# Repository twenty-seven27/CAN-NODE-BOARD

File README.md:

# CAN Node Board — rev A

One custom PCB that replaces the Arduino Mega + CAN Bus Shield stack on every node of a 4WD autonomous parking robot. The robot's three nodes (sensor, receive, motor) talk over CAN; each one now runs the **same board and the same firmware image**, and a single resistor tells the board which node it is.

| | |
|---|---|
| Input | 6–16 V (2S/3S LiPo, 6–8 AA, 12 V bench), reverse-polarity protected, TVS clamped |
| Rails | 5 V / 2 A synchronous buck (servo, ultrasonic sensor, CAN transceiver) · 3.3 V LDO (logic) |
| MCU | STM32G431KBT6 — Cortex-M4F 170 MHz, FDCAN, hardware quadrature-encoder timers |
| CAN | TCAN1042V transceiver, 5 V bus side / 3.3 V logic (VIO), 500 kbit/s classic CAN |
| Board | 76 × 56 mm, 4 layers (signal / GND / 3.3 V / signal), 4 × M3 holes |
| I/O | Servo, HC-SR04 ultrasonic, 2 × wheel encoder, motor driver (PWM + DIR × 2), UART, 2 spare GPIO, SWD |

## The feature worth pointing out: one PCB, one firmware image, every node

PB0 (an ADC input) sits in the middle of a divider: a fixed 10 kΩ pull-up (R4) and a **role resistor R5** to ground. At boot the firmware averages eight ADC samples, picks the nearest bin, and from that sets its CAN IDs, acceptance filters and which peripherals it starts.

| R5 fitted | V(ROLE) | Role |
|---|---|---|
| 0 Ω | 0.00 V | Sensor node (ultrasonic + servo) |
| 3.3 kΩ | 0.82 V | Receive node |
| 10 kΩ | 1.65 V | Motor node (encoders + motor driver) |
| 33 kΩ | 2.53 V | Spare |
| not fitted | 3.30 V | **Safe mode**: CAN listen-only, all outputs off |

- One pin carries five roles. Bins are about 0.8 V apart, so 5 % resistors can never land in the wrong one.
- Nothing to bump or misconfigure later, unlike a DIP switch, and it costs one 0603 part.
- An unfitted board fails safe: it can never drive the motors by accident.
- The same idea runs through the rest of the board: the transceiver's STB pin is pulled **high**, so a node stays off the bus until its firmware is ready, and CAN termination is a pair of solder jumpers (JP1 + JP2, split 2 × 60.4 Ω + 4.7 nF) closed only on the two end-of-bus boards. Every board is identical until it is configured.

The role table is printed on the back silkscreen, so the board documents itself.

## Block diagram

```mermaid
flowchart LR
  BUS["Bus connectors J1/J2<br/>VBAT · GND · CAN-H · CAN-L<br/>(daisy-chained)"] -->|VBAT| PG["Reverse-polarity P-FET Q1<br/>+ Zener D1, TVS D2"]
  PG -->|VIN_PROT| BUCK["5 V buck U1<br/>AP63205, 2 A"]
  BUCK -->|+5V| LDO["3.3 V LDO U2<br/>AP2112K-3.3"]
  BUCK -->|+5V| IO
  BUS <-->|CAN-H/L| XCVR["CAN transceiver U4<br/>TCAN1042V"]
  XCVR --- TERM["Split termination<br/>JP1/JP2, end nodes only"]
  XCVR <-->|TX/RX, STB| MCU["STM32G431KBT6 U3<br/>FDCAN · TIM encoders · ADC"]
  LDO -->|+3V3| MCU
  ROLE["Role select<br/>R4 + R5 → PB0"] --> MCU
  MCU --> IO["Headers: servo, ultrasonic,<br/>encoders, motor, UART, AUX"]
  SWD["SWD J10 (ST-Link)"] --- MCU
```

## Design decisions

**MCU and pins.** The STM32G431 has FDCAN built in (no separate CAN controller as on the MCP2515 shield) and timers with a hardware quadrature-encoder mode for the wheel encoders. On the 32-pin package, FDCAN TX only exists on PA12, which is also USB D+, so CAN and USB cannot both be used. The board drops USB and is programmed over SWD (ST-Link or a Nucleo's built-in one), with a 3-pin UART header for serial debug. PB8 doubles as BOOT0 and is pulled low, so the board always boots from flash.

| Pin | Function |
|---|---|
| PA11 / PA12 | FDCAN1 RX / TX |
| PA13 / PA14 | SWDIO / SWCLK |
| PA2 / PA3 | USART2 TX / RX (debug) |
| PB0 | ADC1_IN15, role select |
| PA0 | TIM2_CH1 input capture (ultrasonic echo, 32-bit timer) |
| PA1 | Ultrasonic trigger |
| PB4 | TIM16_CH1 servo PWM, 50 Hz |
| PA8 / PA9 | TIM1_CH1 / CH2 motor PWM, ~20 kHz |
| PA4 / PA5 | Motor direction |
| PB6 / PB7 | TIM4 encoder mode (left) |
| PA6 / PA7 | TIM3 encoder mode (right) |
| PF0 / PF1 | 8 MHz crystal (HSE) |
| PA10 | Status LED |
| PA15 | Transceiver STB |
| PB3 / PB5 | Spare GPIO on the AUX header |

The servo and the motors run on **different timers** because channels on one timer share a period: a servo needs 50 Hz, a motor driver about 20 kHz.

**Clock.** CAN bit timing needs a tighter clock than the internal RC oscillator gives, so an 8 MHz crystal drives the PLL. Load capacitors: C = 2 × (C_L − C_stray) = 2 × (10 − 3) pF ≈ 15 pF; match them to the crystal actually fitted.

**Power.** Q1 (AO3407A, −30 V, V_GS ±20 V) protects against a reversed battery with almost no voltage drop; the body diode conducts first, then the gate (pulled to ground through R1) turns the FET fully on. D1 clamps V_GS to 12 V and D2 (SMAJ18CA) clamps input transients from the motors. The buck uses the datasheet's typical-application values (10 µF in, 4.7 µH, 2 × 22 µF out, 100 nF bootstrap). C1 (47 µF) damps the input cable's inductance and C17 (220 µF) sits at the servo header to absorb stall-current spikes. VDDA is fed through a ferrite bead because the role pin is an analog measurement.

**Interfaces.** The HC-SR04 echo is a 5 V signal, divided to 3.33 V by R8/R9 (1 k / 2 k). Encoders are powered at 3.3 V with 10 kΩ pull-ups, which suits open-collector Hall encoders; if yours need 5 V, check that their outputs stay within the MCU's input limits. The motor header supplies 5 V for driver logic and takes 3.3 V PWM/DIR.

**Layout.** Four layers: In1 is an unbroken ground plane under everything, In2 is the 3.3 V plane, and the outer layers carry signals with ground pours. Every surface-mount ground and 3.3 V pad has its own via to its plane. The buck's input capacitor sits right next to its VIN and GND pins and the switch node is a short, wide copper run to the inductor. Power nets use 0.6–0.8 mm tracks, CAN-H/L 0.25 mm, signals 0.2 mm, with 0.2 mm clearance and 0.6/0.3 mm vias, all within standard 4-layer capabilities at JLCPCB and PCBWay.

## Verification status

- Schematic connectivity checked against the intended netlist (all 43 nets match); every power-input net has a driver or power flag.
- PCB DRC (KiCad 7.0.11): **0 violations, 0 unconnected pads, 0 footprint errors**.
- **Not yet fabricated or tested.** Bring-up plan for the first boards:
  1. Check for shorts between VBAT, 5 V, 3.3 V and GND before applying power.
  2. Power from a current-limited bench supply (12 V, 100 mA limit) and check 5 V and 3.3 V.
  3. Flash a blink + role-readout firmware over SWD; confirm the status LED blinks the role number.
  4. Two boards on a short bus with JP1/JP2 closed at each end: send and receive frames at 500 kbit/s.
  5. Connect the servo, sensor, encoders and motor driver one at a time.

## Files

| Path | Contents |
|---|---|
| `kicad/` | KiCad project: schematic, PCB, project symbol library (TCAN1042V) |
| `docs/schematic.pdf` | Schematic, one A3 sheet |
| `docs/render-3d.png`, `render-top.png`, `render-bottom.png` | Board renders |
| `docs/layout-top.png`, `layout-bottom.png` | Copper and silkscreen plots (pours hidden) |
| `docs/can-node.step` | 3D model of the assembled board |
| `fab/can-node-gerbers.zip` | Gerbers (4 layers) + Excellon drill files, origin at the board's bottom-left corner |
| `fab/can-node-bom.csv` | Bill of materials (part numbers are examples; R5 is fitted per role) |
| `fab/can-node-cpl.csv` | Pick-and-place positions for assembly |

Ordering: 4 layers, 1.6 mm FR-4, 1 oz outer copper, any surface finish. Upload `can-node-gerbers.zip` as-is.

Designed in KiCad 7; the project opens in KiCad 8 and 9 (KiCad offers to upgrade the file format on first save).

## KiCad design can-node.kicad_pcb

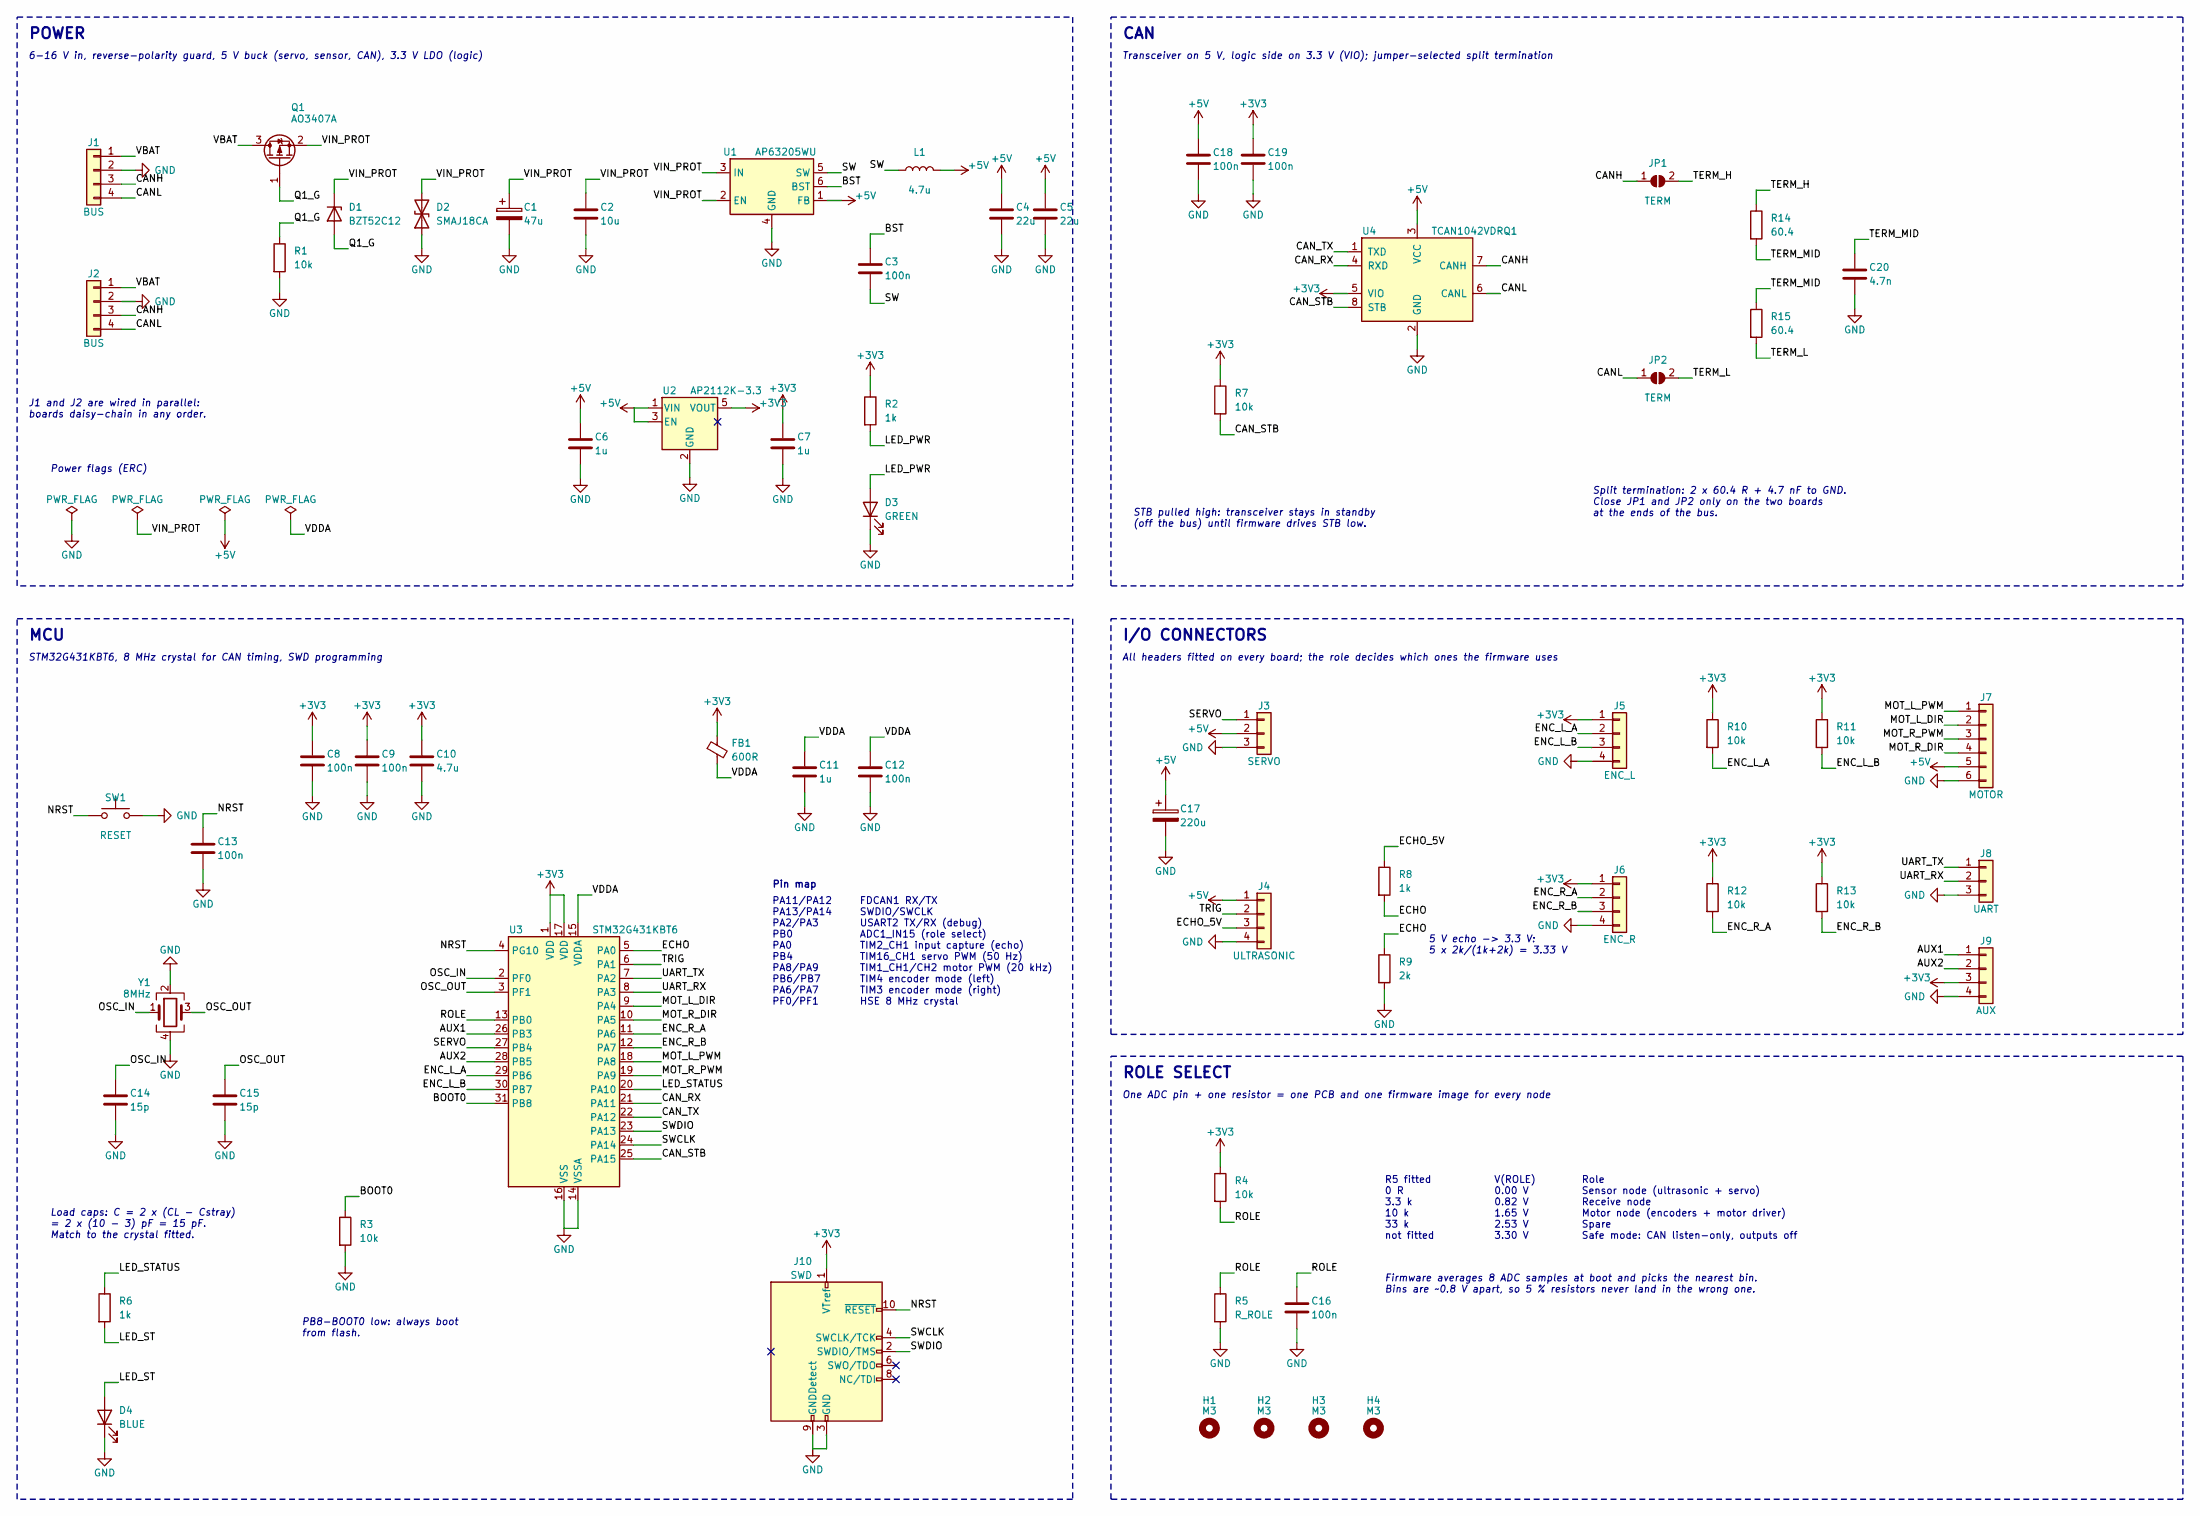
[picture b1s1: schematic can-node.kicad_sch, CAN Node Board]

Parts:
C1: 47u; CP_Elec_6.3x7.7; MPN Aluminium electrolytic 47 uF 35 V 6.3x7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
C2: 10u; C_1206_3216Metric; MPN X5R 10 uF 35 V 1206
C3, C8, C9, C12, C13, C16, C18, C19: 100n; C_0603_1608Metric; MPN X7R 100 nF 50 V 0603
C4, C5: 22u; C_1206_3216Metric; MPN X5R 22 uF 16 V 1206
C6, C7, C11: 1u; C_0603_1608Metric; MPN X7R 1 uF 16 V 0603
C10: 4.7u; C_0603_1608Metric; MPN X5R 4.7 uF 10 V 0603
C14, C15: 15p; C_0603_1608Metric; MPN C0G 15 pF 50 V 0603
C17: 220u; CP_Elec_6.3x7.7; MPN Aluminium electrolytic 220 uF 10 V 6.3x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
C20: 4.7n; C_0603_1608Metric; MPN C0G 4.7 nF 50 V 0603
D1: BZT52C12; D_SOD-123; MPN BZT52C12-7-F
D2: SMAJ18CA; D_SMA; MPN SMAJ18CA
D3: GREEN; LED_0603_1608Metric; MPN Green LED 0603
D4: BLUE; LED_0603_1608Metric; MPN Blue LED 0603
FB1: 600R; L_0603_1608Metric; MPN Murata BLM18AG601SN1D (600 R at 100 MHz)
H1, H2, H3, H4: M3; MountingHole_3.2mm_M3
J1, J2: BUS; JST_XH_B4B-XH-A_1x04_P2.50mm_Vertical; MPN JST B4B-XH-A
J3: SERVO; PinHeader_1x03_P2.54mm_Vertical; MPN 1x3 2.54 mm header
J4: ULTRASONIC; PinHeader_1x04_P2.54mm_Vertical; MPN 1x4 2.54 mm header
J5: ENC_L; PinHeader_1x04_P2.54mm_Vertical; MPN 1x4 2.54 mm header
J6: ENC_R; PinHeader_1x04_P2.54mm_Vertical; MPN 1x4 2.54 mm header
J7: MOTOR; PinHeader_1x06_P2.54mm_Vertical; MPN 1x6 2.54 mm header
J8: UART; PinHeader_1x03_P2.54mm_Vertical; MPN 1x3 2.54 mm header
J9: AUX; PinHeader_1x04_P2.54mm_Vertical; MPN 1x4 2.54 mm header
J10: SWD; PinHeader_2x05_P1.27mm_Vertical_SMD; MPN 2x5 1.27 mm SMD header (Cortex debug)
JP1, JP2: TERM; SolderJumper-2_P1.3mm_Open_RoundedPad1.0x1.5mm
L1: 4.7u; L_Bourns_SRN6045TA; MPN Bourns SRN6045TA-4R7M
Q1: AO3407A; SOT-23; MPN AO3407A
R1, R3, R7, R10, R11, R12, R13: 10k; R_0603_1608Metric
R2, R6, R8: 1k; R_0603_1608Metric
R4: 10k; R_0603_1608Metric; MPN 10k 1% 0603
R5: R_ROLE; R_0603_1608Metric; MPN per role table
R9: 2k; R_0603_1608Metric
R14, R15: 60.4; R_0603_1608Metric; MPN 60.4 ohm 1% 0603
SW1: RESET; SW_SPST_TL3342; MPN E-Switch TL3342F160QG
U1: AP63205WU; TSOT-23-6; MPN AP63205WU-7
U2: AP2112K-3.3; SOT-23-5; MPN AP2112K-3.3TRG1
U3: STM32G431KBT6; LQFP-32_7x7mm_P0.8mm; MPN STM32G431KBT6
U4: TCAN1042VDRQ1; SOIC-8_3.9x4.9mm_P1.27mm; MPN TCAN1042VDRQ1
Y1: 8MHz; Crystal_SMD_3225-4Pin_3.2x2.5mm; MPN 8 MHz 3225 crystal, CL = 10 pF, +/-20 p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

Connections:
+3V3: C7.1, C8.1, C9.1, C10.1, C19.1, FB1.1, J5.1, J6.1, J9.3, J10.1 (VTref), R2.1, R4.1, R7.1, R10.1, R11.1, R12.1, R13.1, U2.5 (VOUT), U3.1 (VDD), U3.17 (VDD), U4.5 (VIO)
+5V: C4.1, C5.1, C6.1, C17.1, C18.1, J3.2, J4.1, J7.5, L1.2, U1.1 (FB), U2.1 (VIN), U2.3 (EN), U4.3 (VCC)
/AUX1: J9.1, U3.26 (PB3)
/AUX2: J9.2, U3.28 (PB5)
/BOOT0: R3.1, U3.31 (PB8)
/BST: C3.1, U1.6 (BST)
/CANH: J1.3, J2.3, JP1.1 (A), U4.7 (CANH)
/CANL: J1.4, J2.4, JP2.1 (A), U4.6 (CANL)
/CAN_RX: U3.21 (PA11), U4.4 (RXD)
/CAN_STB: R7.2, U3.25 (PA15), U4.8 (STB)
/CAN_TX: U3.22 (PA12), U4.1 (TXD)
/ECHO: R8.2, R9.1, U3.5 (PA0)
/ECHO_5V: J4.3, R8.1
/ENC_L_A: J5.2, R10.2, U3.29 (PB6)
/ENC_L_B: J5.3, R11.2, U3.30 (PB7)
/ENC_R_A: J6.2, R12.2, U3.11 (PA6)
/ENC_R_B: J6.3, R13.2, U3.12 (PA7)
/LED_PWR: D3.2 (A), R2.2
/LED_ST: D4.2 (A), R6.2
/LED_STATUS: R6.1, U3.20 (PA10)
/MOT_L_DIR: J7.2, U3.9 (PA4)
/MOT_L_PWM: J7.1, U3.18 (PA8)
/MOT_R_DIR: J7.4, U3.10 (PA5)
/MOT_R_PWM: J7.3, U3.19 (PA9)
/NRST: C13.1, J10.10 (~RESET), SW1.1, U3.4 (PG10)
/OSC_IN: C14.1, U3.2 (PF0), Y1.1
/OSC_OUT: C15.1, U3.3 (PF1), Y1.3
/Q1_G: D1.2 (A), Q1.1 (G), R1.1
/ROLE: C16.1, R4.2, R5.1, U3.13 (PB0)
/SERVO: J3.1, U3.27 (PB4)
/SW: C3.2, L1.1, U1.5 (SW)
/SWCLK: J10.4 (SWCLK/TCK), U3.24 (PA14)
/SWDIO: J10.2 (SWDIO/TMS), U3.23 (PA13)
/TERM_H: JP1.2 (B), R14.1
/TERM_L: JP2.2 (B), R15.2
/TERM_MID: C20.1, R14.2, R15.1
/TRIG: J4.2, U3.6 (PA1)
/UART_RX: J8.2, U3.8 (PA3)
/UART_TX: J8.1, U3.7 (PA2)
/VBAT: J1.1, J2.1, Q1.3 (D)
/VDDA: C11.1, C12.1, FB1.2, U3.15 (VDDA)
/VIN_PROT: C1.1, C2.1, D1.1 (K), D2.2 (A2), Q1.2 (S), U1.2 (EN), U1.3 (IN)
GND: C1.2, C2.2, C4.2, C5.2, C6.2, C7.2, C8.2, C9.2, C10.2, C11.2, C12.2, C13.2, C14.2, C15.2, C16.2, C17.2, C18.2, C19.2, C20.2, D2.1 (A1), D3.1 (K), D4.1 (K), J1.2, J2.2, J3.3, J4.4, J5.4, J6.4, J7.6, J8.3, J9.4, J10.3 (GND), J10.5 (GND), J10.9 (GNDDetect), R1.2, R3.2, R5.2, R9.2, SW1.2, U1.4 (GND), U2.2 (GND), U3.14 (VSSA), U3.16 (VSS), U3.32 (VSS), U4.2 (GND), Y1.2, Y1.4

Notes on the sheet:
POWER
6-16 V in, reverse-polarity guard, 5 V buck (servo, sensor, CAN), 3.3 V LDO (logic)
J1 and J2 are wired in parallel: boards daisy-chain in any order.
Power flags (ERC)
CAN
Transceiver on 5 V, logic side on 3.3 V (VIO); jumper-selected split termination
STB pulled high: transceiver stays in standby (off the bus) until firmware drives STB low.
Split termination: 2 x 60.4 R + 4.7 nF to GND. Close JP1 and JP2 only on the two boards at the ends of the bus.
MCU
STM32G431KBT6, 8 MHz crystal for CAN timing, SWD programming
Pin map
PA11/PA12 PA13/PA14 PA2/PA3 PB0 PA0 PB4 PA8/PA9 PB6/PB7 PA6/PA7 PF0/PF1
FDCAN1 RX/TX SWDIO/SWCLK USART2 TX/RX (debug) ADC1_IN15 (role select) TIM2_CH1 input capture (echo) TIM16_CH1 servo PWM (50 Hz) TIM1_CH1/CH2 motor PWM (20 kHz) TIM4 encoder mode (left) TIM3 encoder mode (right) HSE 8 MHz crystal
Load caps: C = 2 x (CL - Cstray) = 2 x (10 - 3) pF = 15 pF. Match to the crystal fitted.
PB8-BOOT0 low: always boot from flash.
I/O CONNECTORS
All headers fitted on every board; the role decides which ones the firmware uses
5 V echo -> 3.3 V: 5 x 2k/(1k+2k) = 3.33 V
ROLE SELECT
One ADC pin + one resistor = one PCB and one firmware image for every node
R5 fitted 0 R 3.3 k 10 k 33 k not fitted
V(ROLE) 0.00 V 0.82 V 1.65 V 2.53 V 3.30 V
Role Sensor node (ultrasonic + servo) Receive node Motor node (encoders + motor driver) Spare Safe mode: CAN listen-only, outputs off
Firmware averages 8 ADC samples at boot and picks the nearest bin. Bins are ~0.8 V apart, so 5 % resistors never land in the wrong one.

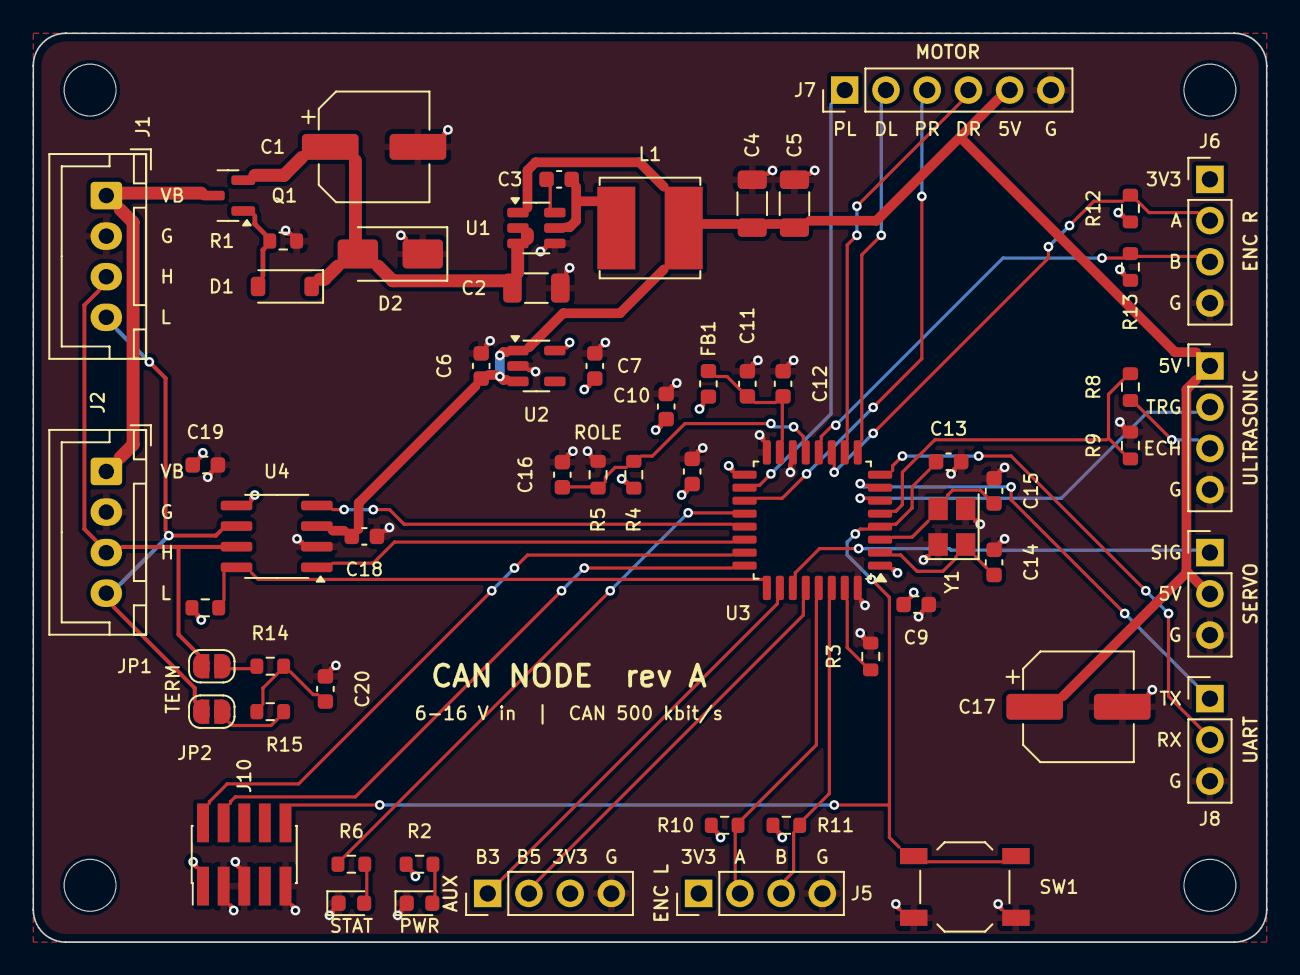
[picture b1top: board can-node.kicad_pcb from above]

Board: 4 copper layers, 76.0 x 56.0 mm, 64 parts (0 on the bottom side), 43 nets.
